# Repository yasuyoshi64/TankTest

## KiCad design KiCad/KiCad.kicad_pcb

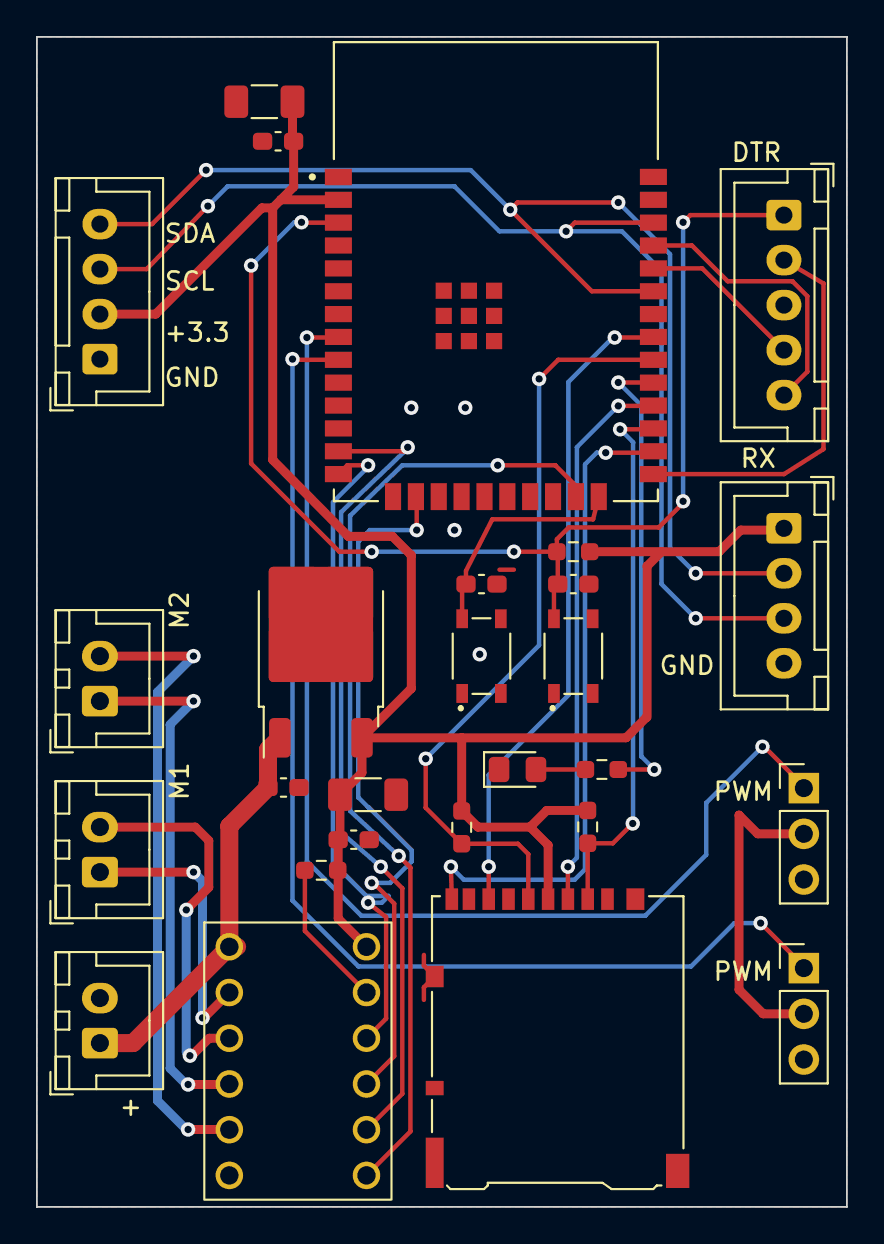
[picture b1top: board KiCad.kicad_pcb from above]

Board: 2 copper layers, 45.0 x 65.0 mm, 27 parts (0 on the bottom side), 28 nets.

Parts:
C1, C2, C4, C6, C7: 0.1μ; C_0603_1608Metric_Pad1.08x0.95mm_HandSolder
C3, C5: 22μ; C_1206_3216Metric_Pad1.33x1.80mm_HandSolder
D1: TLRE1002A; LED_0805_2012Metric_Pad1.15x1.40mm_HandSolder
J1: 3.7v; JST_XH_B2B-XH-A_1x02_P2.50mm_Vertical
J2: writer; JST_XH_B5B-XH-A_1x05_P2.50mm_Vertical
J3: SSD1306; JST_XH_B4B-XH-A_1x04_P2.50mm_Vertical
J4: Micro_SD_Card_DW3AT-SF-PFJM5; microSD_HC_Hirose_DM3AT-SF-PEJM5
J5: MotorA; JST_XH_B2B-XH-A_1x02_P2.50mm_Vertical
J6: MotorB; JST_XH_B2B-XH-A_1x02_P2.50mm_Vertical
J7: SPI; JST_XH_B4B-XH-A_1x04_P2.50mm_Vertical
M1, M2: SG90; PinHeader_1x03_P2.54mm_Vertical
R1: 330; R_0603_1608Metric_Pad0.98x0.95mm_HandSolder
R2, R3, R4, R5: 10k; R_0603_1608Metric_Pad0.98x0.95mm_HandSolder
S1, S2: SKRPACE010; SW_SKRPACE010
U1: NJM2845DL1-33; TO-252-2
U2: ESP32-WROOM-32E_16MB; ESP32-WROOM-32E__16MB
U3: DRV8835 Module; DRV8835-Module

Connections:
3.7v: C1.1, J1.1, M1.2 (+), M2.2 (+), U1.1 (VI), U3.1 (VM)
+3.3V: C2.1, C3.1, C4.1, C5.1, J3.2 (VCC), J4.4 (VDD), J7.1, R2.1, R3.1, R4.1, R5.1, U1.3 (VO), U2.2 (3V3), U3.12 (VCC)
/IO4: J4.9 (DET_B), U2.26 (IO4)
/IO12: U2.14 (IO12), U3.10 (AIN1)
/IO13: U2.16 (IO13), U3.9 (AIN2)
/IO14: U2.13 (IO14), U3.8 (BIN1)
/IO15: U2.23 (IO15), U3.7 (BIN2)
/IO16: J4.2 (DAT3/CD), R3.2, U2.27 (IO16)
/IO17: J4.3 (CMD), U2.28 (IO17)
/IO18: J4.5 (CLK), R4.2, U2.30 (IO18)
/IO19: J4.7 (DAT0), U2.31 (IO19)
/IO32: M1.1 (PWM), U2.8 (IO32)
/IO33: M2.1 (PWM), U2.9 (IO33)
DTR: C6.1, J2.1, R2.2, S1.2, U2.3 (EN)
GND: C1.2, C2.2, C3.2, C4.2, C5.2, C6.2, C7.2, D1.1 (K), J1.2, J2.3, J3.1 (GND), J4.6 (VSS), J4.10 (DET_A), J4.11 (SHIELD), J7.4, M1.3 (-), M2.3 (-), S1.4, S2.4, U1.2 (GND), U2.1 (GND), U2.15 (GND), U2.38 (GND), U2.39_1 (GND), U2.39_2 (GND), U2.39_3 (GND), U2.39_4 (GND), U2.39_5 (GND), U2.39_6 (GND), U2.39_7 (GND), U2.39_8 (GND), U2.39_9 (GND), U3.6 (GND)
unnamed: D1.2 (A), R1.2
unnamed: J5.1, U3.2 (AOUT1)
unnamed: J5.2, U3.3 (AOUT2)
unnamed: J6.1, U3.4 (BOUT1)
unnamed: J6.2, U3.5 (BOUT2)
unnamed: C7.1, S2.2, U2.24 (IO2)
unnamed: R1.1, U2.29 (IO5)
unnamed: R5.2, U3.11 (MODE)
RTS: J2.2, U2.25 (IO0)
RX: J2.5, U2.35 (TXD0)
SCL: J3.3 (SCL), J7.3, U2.36 (IO22)
SDA: J3.4 (SDA), J7.2, U2.33 (IO21)
TX: J2.4, U2.34 (RXD0)

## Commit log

2024-05-20 初期コミット
2024-05-20 bin追加
2024-06-02 モーターの出力アップ時に100ms単位で徐々に上げるように修正
